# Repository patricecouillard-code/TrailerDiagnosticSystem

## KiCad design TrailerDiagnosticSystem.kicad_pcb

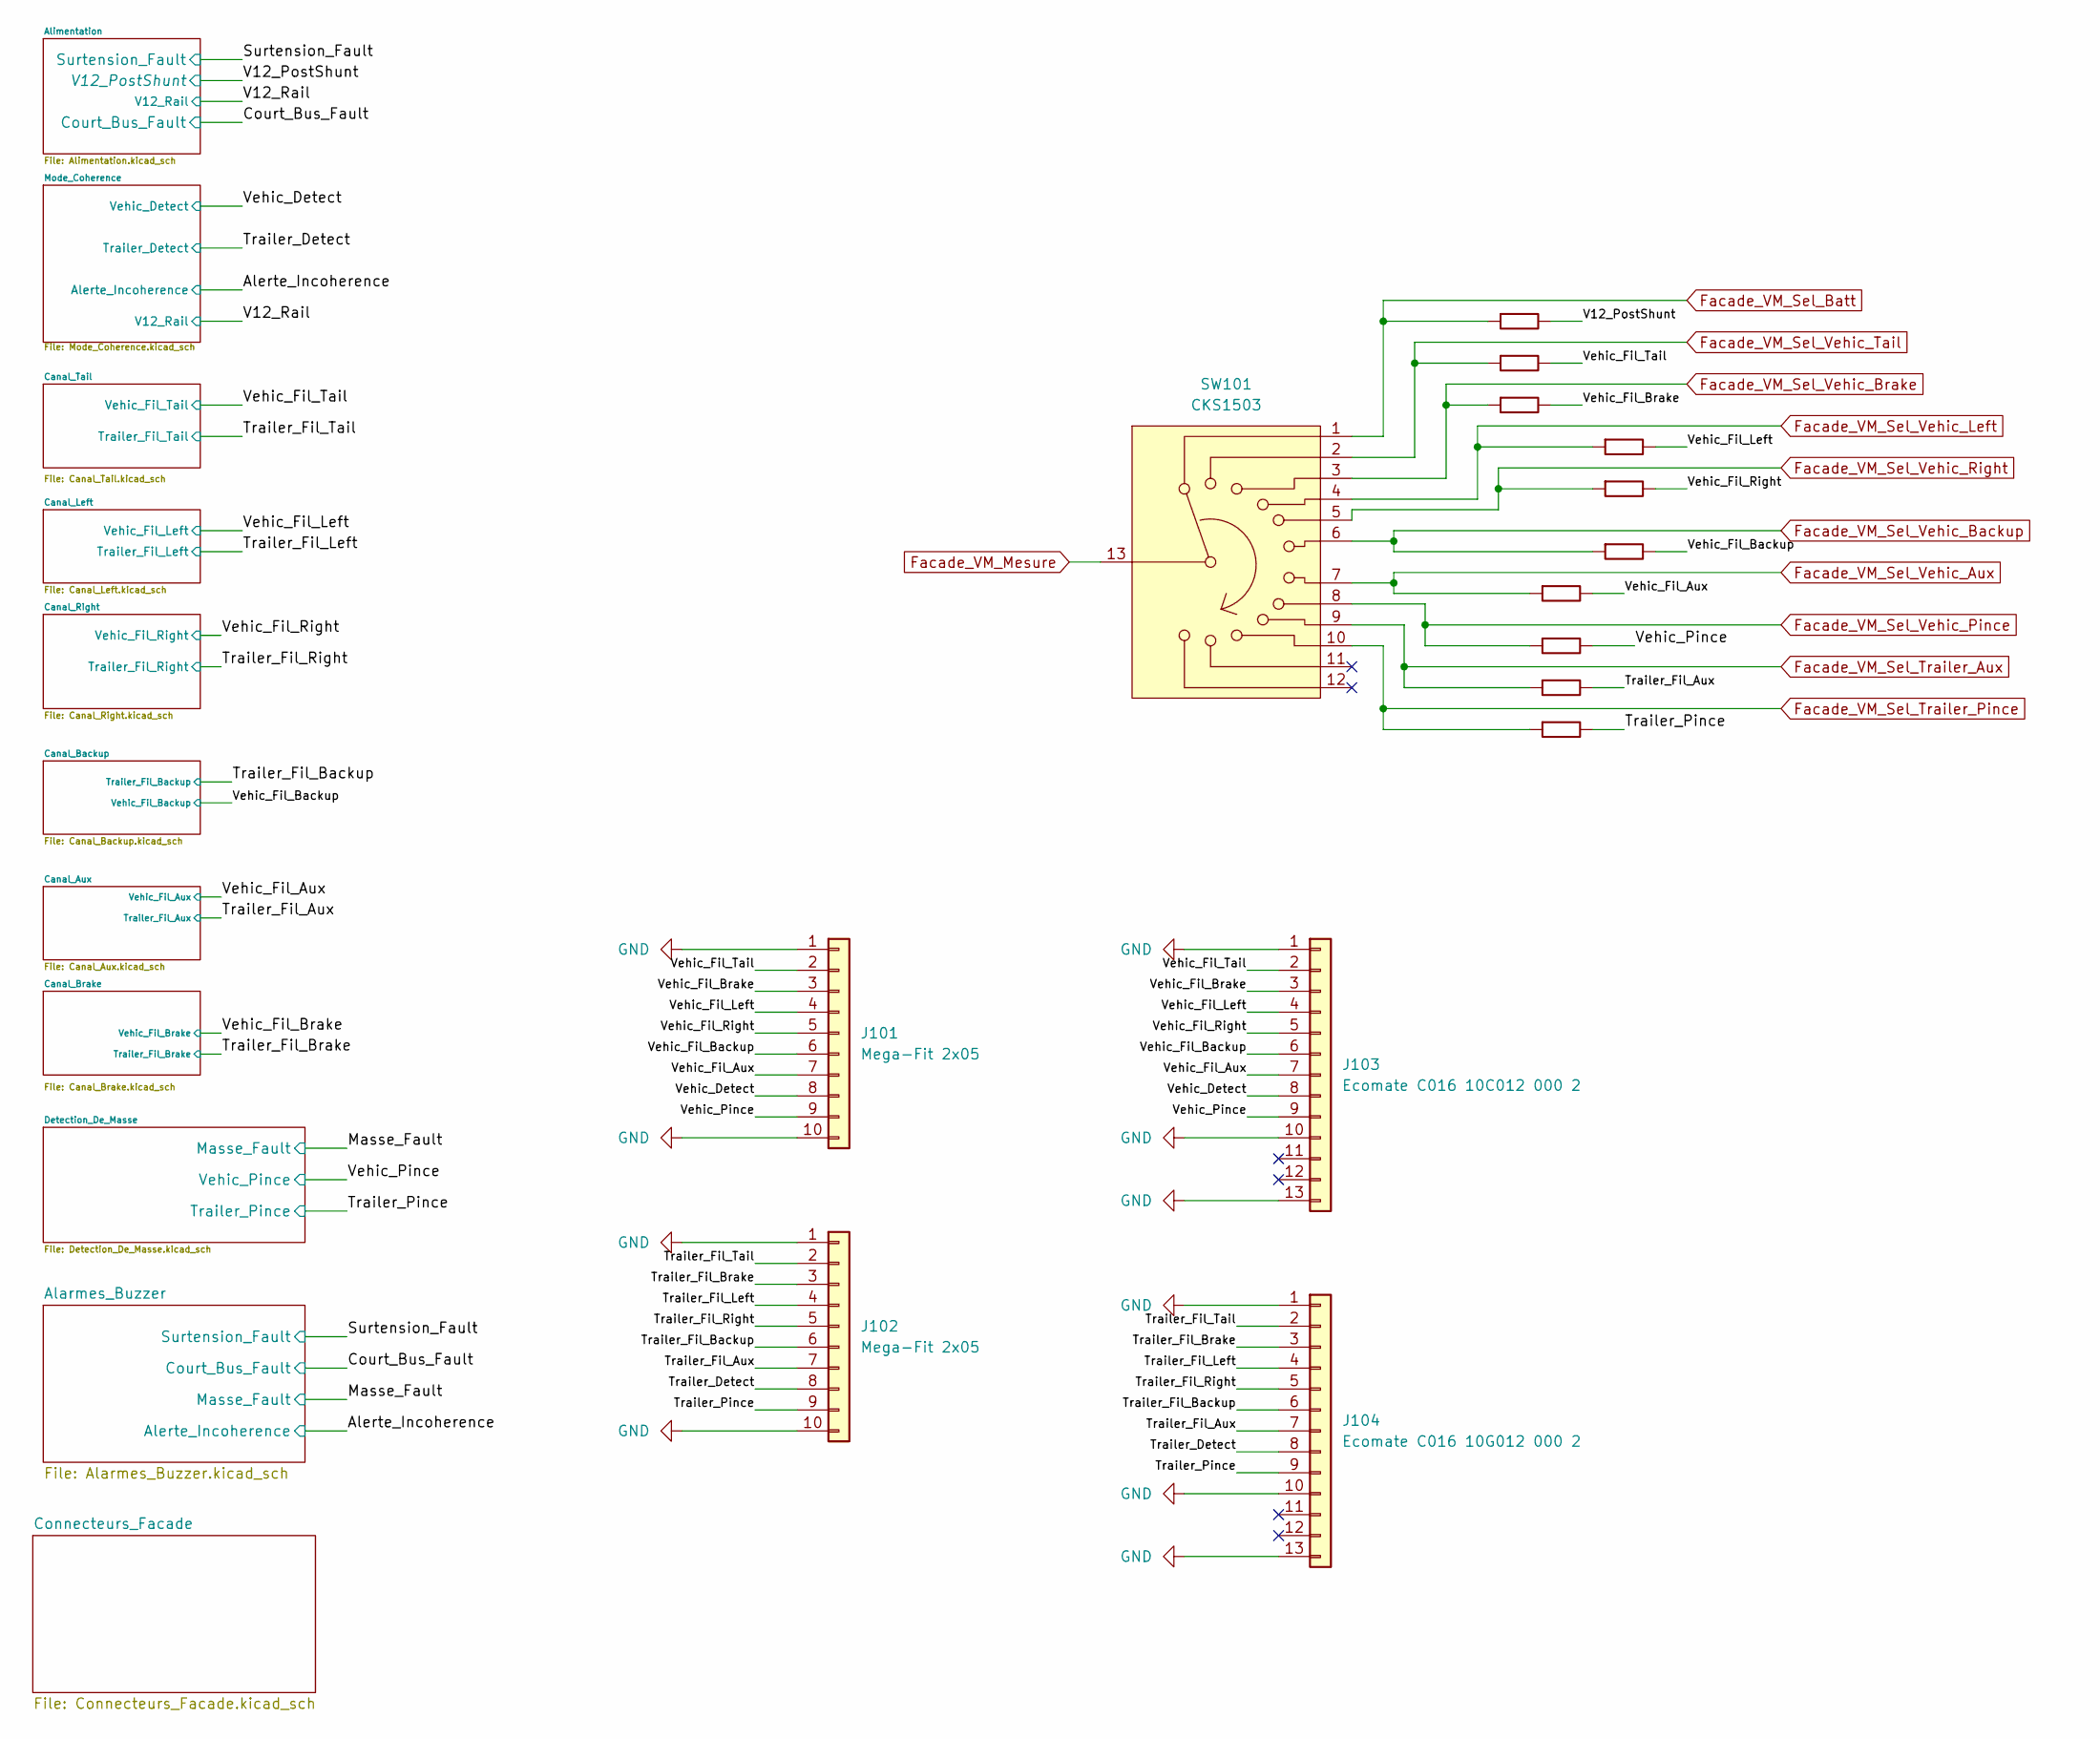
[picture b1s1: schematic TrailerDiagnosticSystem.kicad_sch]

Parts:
J101, J102: Mega-Fit 2x05; Molex_Mega-Fit_76829-0010_2x05_P5.70mm_Vertical
J103: Ecomate C016 10C012 000 2
J104: Ecomate C016 10G012 000 2
R101, R102, R103, R104, R105, R106, R107, R108, R109, R110: 1kΩ; R_Axial_DIN0309_L9.0mm_D3.2mm_P12.70mm_Horizontal
SW101: CKS1503

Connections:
/Trailer_Detect: J102.8, J104.8; also elsewhere on the board
/Trailer_Fil_Aux: J102.7, J104.7, R106.2; also elsewhere on the board
/Trailer_Fil_Backup: J102.6, J104.6; also elsewhere on the board
/Trailer_Fil_Brake: J102.3, J104.3; also elsewhere on the board
/Trailer_Fil_Left: J102.4, J104.4; also elsewhere on the board
/Trailer_Fil_Right: J102.5, J104.5; also elsewhere on the board
/Trailer_Fil_Tail: J102.2, J104.2; also elsewhere on the board
/Trailer_Pince: J102.9, J104.9, R107.2; also elsewhere on the board
/V12_PostShunt: R101.2; also elsewhere on the board
/Vehic_Detect: J101.8, J103.8; also elsewhere on the board
/Vehic_Fil_Aux: J101.7, J103.7, R104.2; also elsewhere on the board
/Vehic_Fil_Backup: J101.6, J103.6, R110.2; also elsewhere on the board
/Vehic_Fil_Brake: J101.3, J103.3, R103.2; also elsewhere on the board
/Vehic_Fil_Left: J101.4, J103.4, R108.2; also elsewhere on the board
/Vehic_Fil_Right: J101.5, J103.5, R109.2; also elsewhere on the board
/Vehic_Fil_Tail: J101.2, J103.2, R102.2; also elsewhere on the board
/Vehic_Pince: J101.9, J103.9, R105.2; also elsewhere on the board
Facade_VM_Sel_Batt: R101.1, SW101.1; also elsewhere on the board
Facade_VM_Sel_Trailer_Aux: R106.1, SW101.9; also elsewhere on the board
Facade_VM_Sel_Trailer_Pince: R107.1, SW101.10; also elsewhere on the board
Facade_VM_Sel_Vehic_Aux: R104.1, SW101.7; also elsewhere on the board
Facade_VM_Sel_Vehic_Backup: R110.1, SW101.6; also elsewhere on the board
Facade_VM_Sel_Vehic_Brake: R103.1, SW101.3; also elsewhere on the board
Facade_VM_Sel_Vehic_Left: R108.1, SW101.4; also elsewhere on the board
Facade_VM_Sel_Vehic_Pince: R105.1, SW101.8; also elsewhere on the board
Facade_VM_Sel_Vehic_Right: R109.1, SW101.5; also elsewhere on the board
Facade_VM_Sel_Vehic_Tail: R102.1, SW101.2; also elsewhere on the board
GND: J101.1, J101.10, J102.1, J102.10, J103.1, J103.10, J103.13, J104.1, J104.10, J104.13; also elsewhere on the board

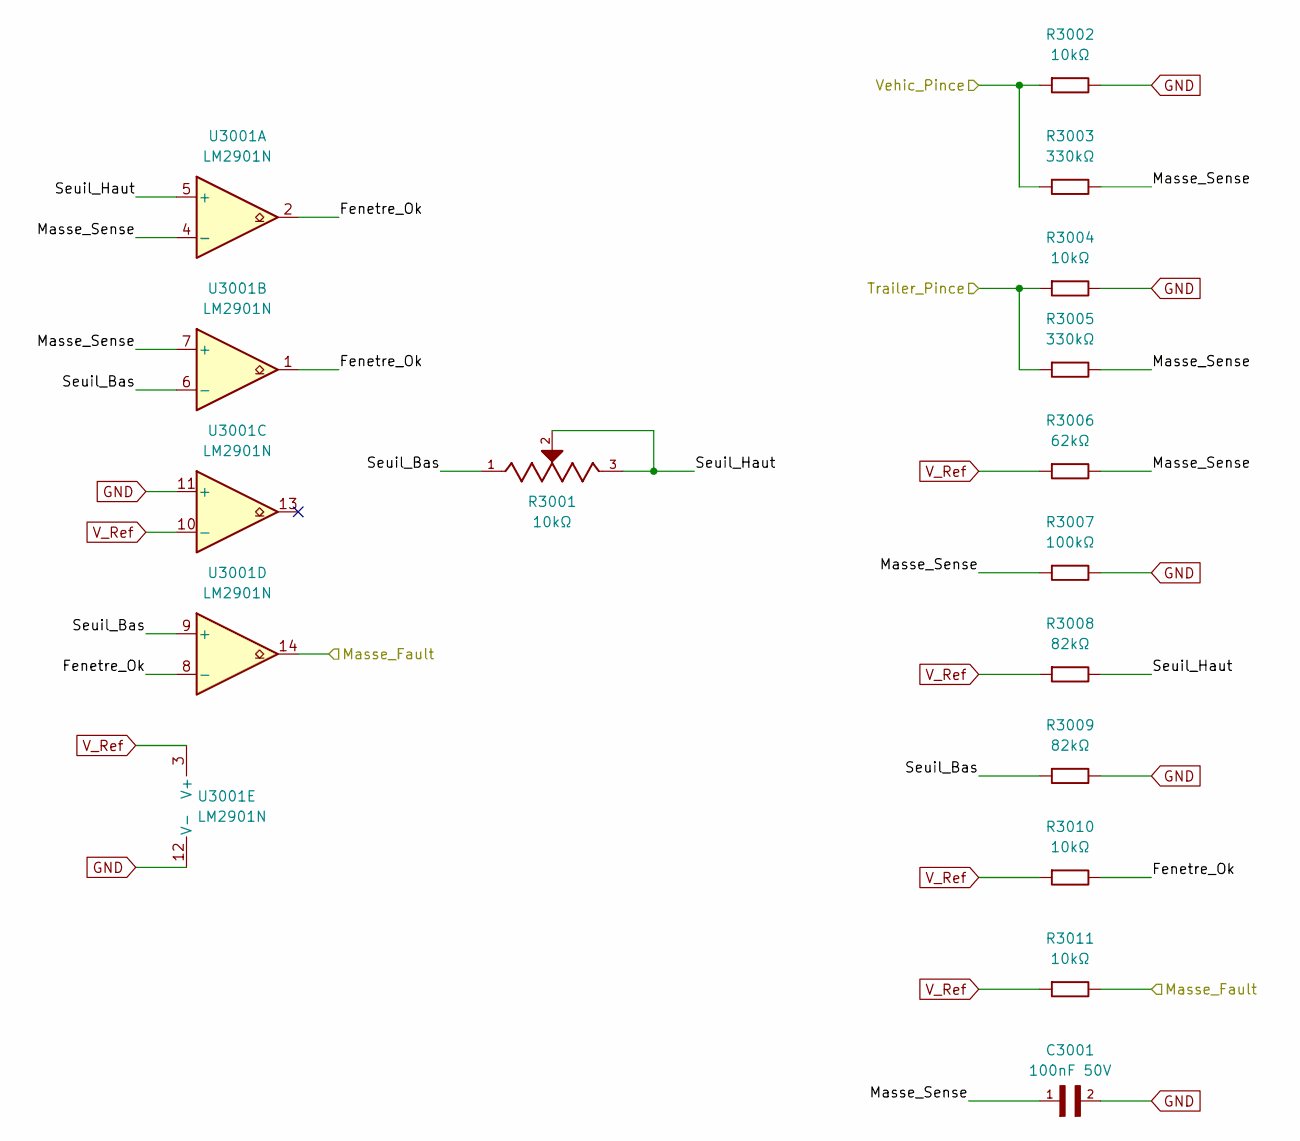
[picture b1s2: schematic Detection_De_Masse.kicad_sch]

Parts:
C3001: 100nF 50V; CAPRR254W50L508T317H508; MPN SR205C104KAR
R3001: 10kΩ; TRIM_3296W1103LF; MPN 3296W-1-103LF
R3002, R3004, R3010, R3011: 10kΩ; R_Axial_DIN0207_L6.3mm_D2.5mm_P10.16mm_Horizontal
R3003, R3005: 330kΩ; R_Axial_DIN0207_L6.3mm_D2.5mm_P10.16mm_Horizontal
R3006: 62kΩ; R_Axial_DIN0207_L6.3mm_D2.5mm_P10.16mm_Horizontal
R3007: 100kΩ; R_Axial_DIN0207_L6.3mm_D2.5mm_P10.16mm_Horizontal
R3008, R3009: 82kΩ; R_Axial_DIN0207_L6.3mm_D2.5mm_P10.16mm_Horizontal
U3001: LM2901N; DIP-14_W7.62mm_Socket

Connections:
/Detection_De_Masse/Fenetre_Ok: R3010.2, U3001.1, U3001.2, U3001.8 (-)
/Detection_De_Masse/Masse_Sense: C3001.1, R3003.2, R3005.2, R3006.2, R3007.1, U3001.4 (-), U3001.7 (+)
/Detection_De_Masse/Seuil_Bas: R3001.1, R3009.1, U3001.6 (-), U3001.9 (+)
/Detection_De_Masse/Seuil_Haut: R3001.2, R3001.3, R3008.2, U3001.5 (+)
/Masse_Fault: R3011.2, U3001.14; also elsewhere on the board
/Trailer_Pince: R3004.1, R3005.1; also elsewhere on the board
/Vehic_Pince: R3002.1, R3003.1; also elsewhere on the board
GND: C3001.2, R3002.2, R3004.2, R3007.2, R3009.2, U3001.11 (+), U3001.12 (V-); also elsewhere on the board
V_Ref: R3006.1, R3008.1, R3010.1, R3011.1, U3001.3 (V+), U3001.10 (-); also elsewhere on the board

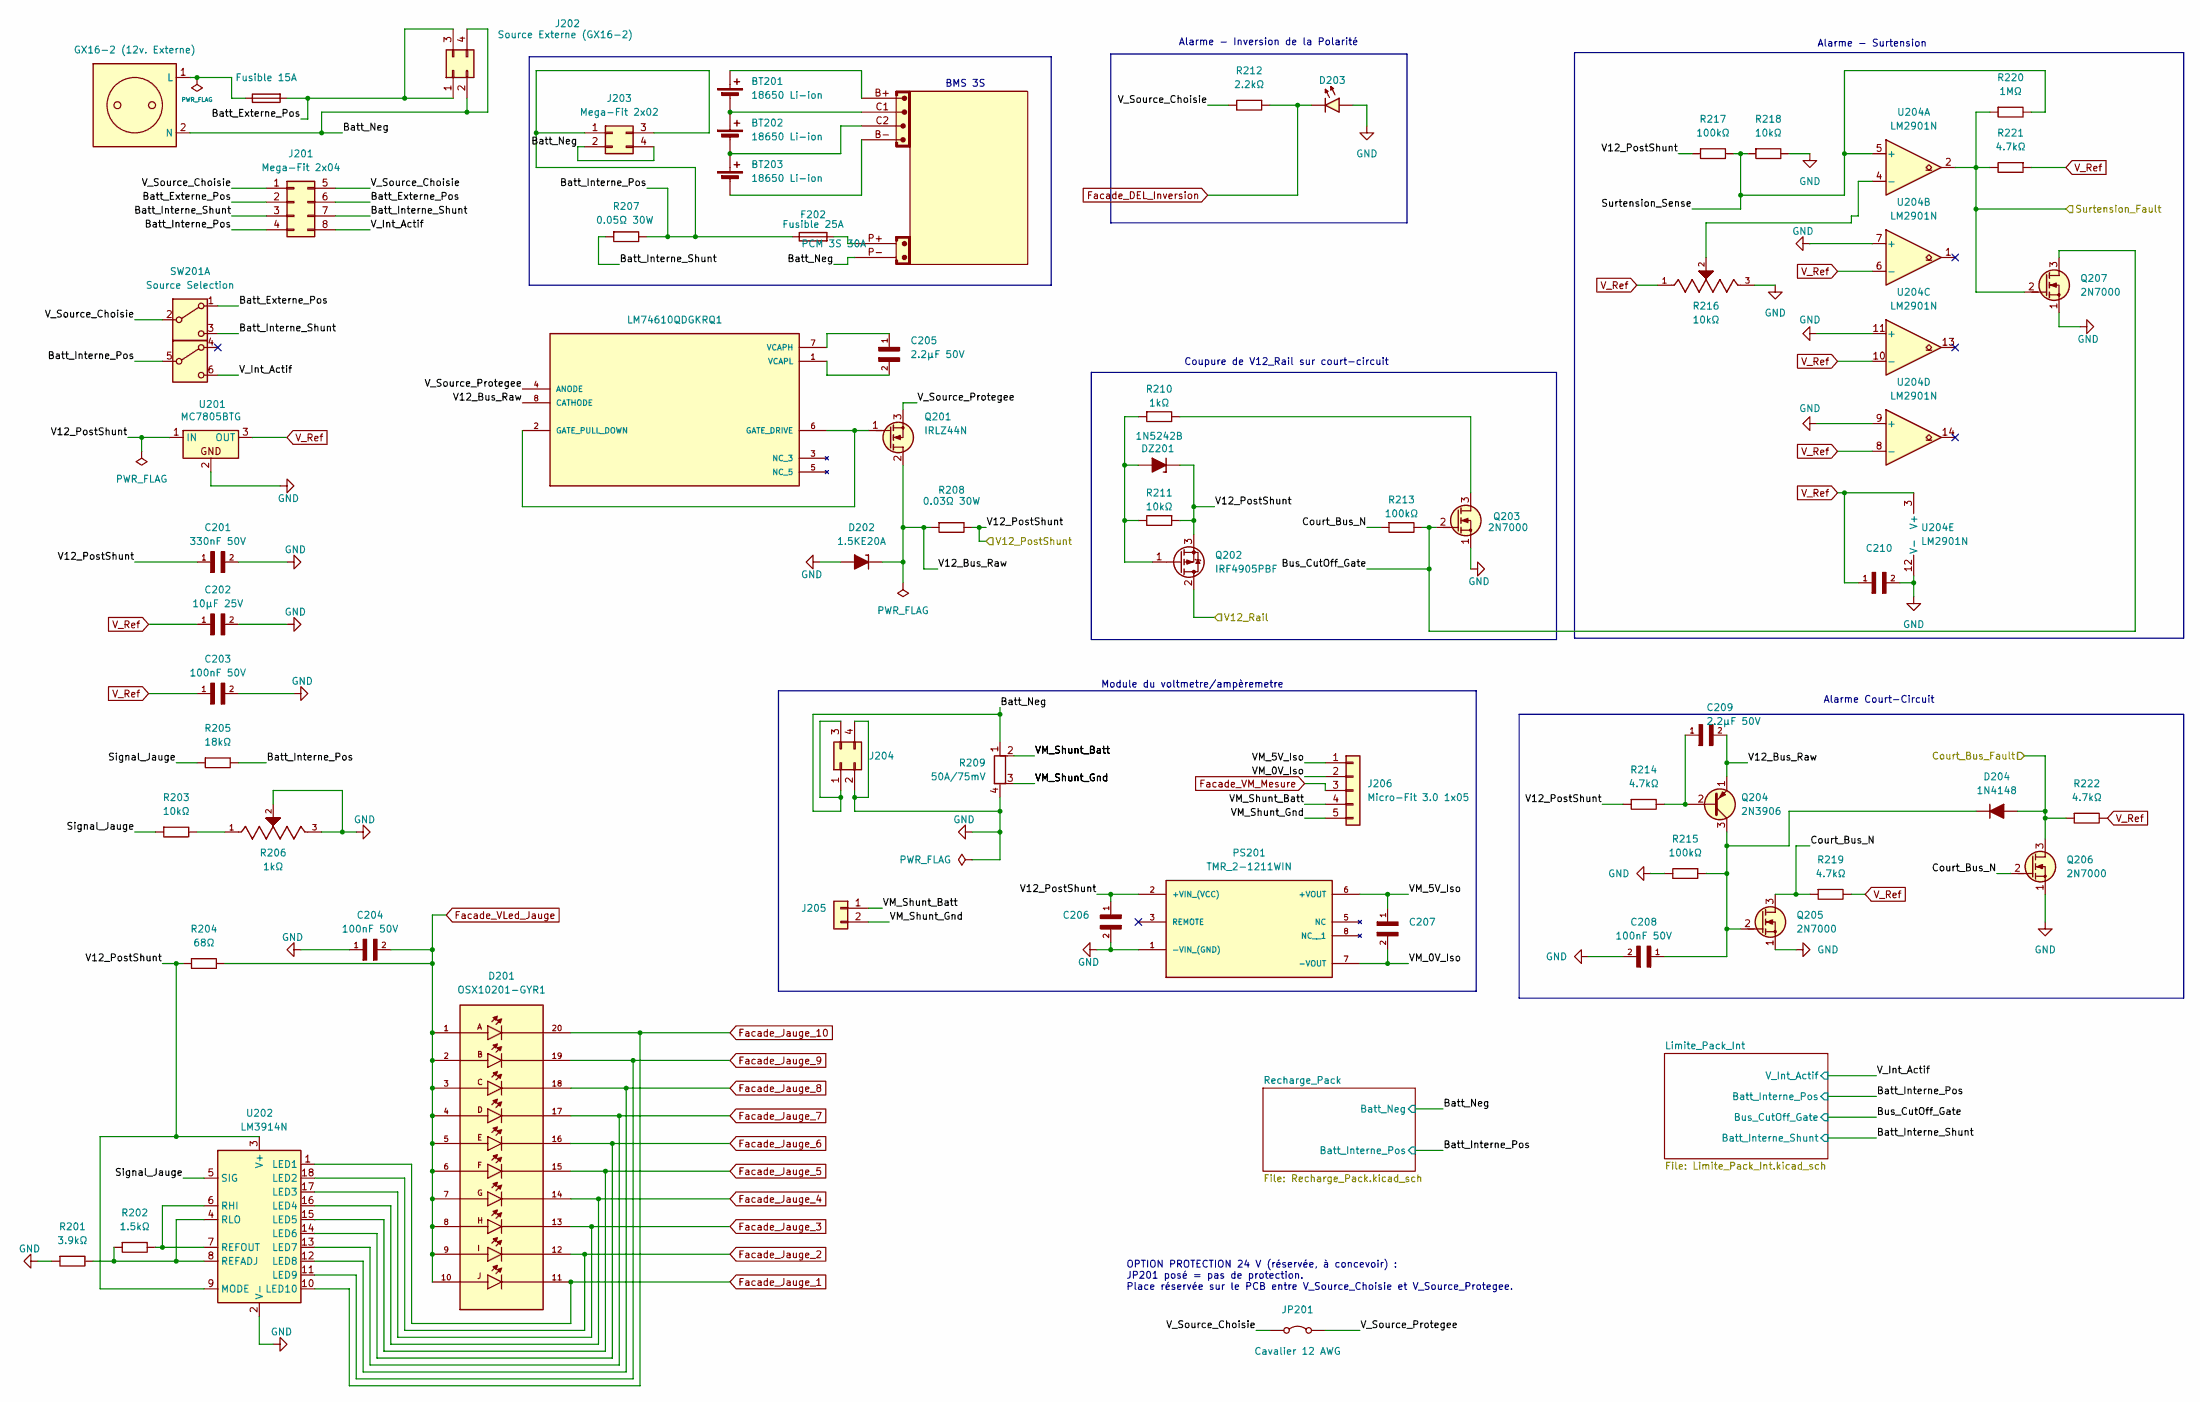
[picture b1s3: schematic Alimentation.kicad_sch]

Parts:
BMS201: PCM 3S 30A; MPN PCM-L04S30-566 (CU-J881, produit #7758)
BT201, BT202, BT203: 18650 Li-ion; MPN INR-18650-P28A
C201: 330nF 50V; CAPRR508W50L762T381H762; MPN SR305C334KAR
C202, C207: 10µF 25V; CAPRB500W50L550T350H600; MPN FG26X7R1E106KRT06
C203, C204, C208, C210: 100nF 50V; CAPRR254W50L508T317H508; MPN SR205C104KAR
C205, C209: 2.2µF 50V; CAPRB500W50L450T300H550; MPN FG24X7R1H225KRT06
C206: 10µF 50V; CAPRR508W50L762T381H762; MPN SR655C106KAR
D201: OSX10201-GYR1; DIP760W45P254L2550H815Q20B; PARTREV VER D.1.0
D202: 1.5KE20A; D_DO-201AE_P15.24mm_Horizontal
D203: RGB 5mm CA (rouge); LED_D5.0mm-4_RGB_Staggered_Pins; MPN WP154A4SEJ3VBDZGW/CA
D204: 1N4148; D_DO-35_SOD27_P7.62mm_Horizontal
DZ201: 1N5242B; D_DO-35_SOD27_P7.62mm_Horizontal_Zener
F201: Fusible 15A; MPN 0287015.PXCN
F202: Fusible 25A; MPN 0287025.PXCN
J201: Mega-Fit 2x04; Molex_Mega-Fit_76829-0008_2x04_P5.70mm_Vertical; MPN 0768290008
J202, J203, J204: Mega-Fit 2x02; Molex_Mega-Fit_76829-0004_2x02_P5.70mm_Vertical; MPN 0768290004
J205: Micro-Fit 3.0 1x02; Molex_Micro-Fit_3.0_43650-0215_1x02_P3.00mm_Vertical
J206: Micro-Fit 3.0 1x05; Molex_Micro-Fit_3.0_43650-0515_1x05_P3.00mm_Vertical
JP201: Cavalier 12 AWG; SolderWire-2.5sqmm_1x02_P8.8mm_D2.4mm_OD4.4mm
P201: Batt. ext. 2P
PS201: TMR_2-1211WIN; CONV_TMR_2-1211WIN; PARTREV January 27, 2021
Q201: IRLZ44N; TO-220-3_Vertical_GDS
Q202: IRF4905PBF; TO-220-3_Vertical; MPN IRF4905PBF
Q203, Q205, Q206, Q207: 2N7000; TO-92_Inline_Wide_SGD
Q204: 2N3906; TO-92_Inline_Wide_EBC
R201: 3.9kΩ; R_Axial_DIN0207_L6.3mm_D2.5mm_P10.16mm_Horizontal
R202: 1.5kΩ; R_Axial_DIN0207_L6.3mm_D2.5mm_P10.16mm_Horizontal
R203, R211, R218: 10kΩ; R_Axial_DIN0207_L6.3mm_D2.5mm_P10.16mm_Horizontal
R204: 68Ω; R_Axial_Power_L25.0mm_W9.0mm_P27.94mm
R205: 18kΩ; R_Axial_DIN0207_L6.3mm_D2.5mm_P10.16mm_Horizontal
R206: 1kΩ; TRIM_3296W-1-102LF; MPN 3296W-1-102LF
R207: 0.05Ω 30W; TO-220-2_Vertical; MPN MP930-0.050-1%
R208: 0.03Ω 30W; TO-220-2_Vertical; MPN MP930-0.030-5%
R209: 50A/75mV
R210: 1kΩ; R_Axial_DIN0207_L6.3mm_D2.5mm_P10.16mm_Horizontal
R212: 2.2kΩ; R_Axial_DIN0207_L6.3mm_D2.5mm_P10.16mm_Horizontal
R213, R215, R217: 100kΩ; R_Axial_DIN0207_L6.3mm_D2.5mm_P10.16mm_Horizontal
R214, R219, R221, R222: 4.7kΩ; R_Axial_DIN0207_L6.3mm_D2.5mm_P10.16mm_Horizontal
R216: 10kΩ; TRIM_3296W1103LF; MPN 3296W-1-103LF
R220: 1MΩ; R_Axial_DIN0207_L6.3mm_D2.5mm_P10.16mm_Horizontal
SW201: Cole Hersee 5592
U201: MC7805BTG; TO-220-3_Vertical
U202: LM3914N; DIP-18_W7.62mm_Socket
U203: LM74610QDGKRQ1; SOP65P490X110-8N; PARTREV B
U204: LM2901N; DIP-14_W7.62mm_Socket

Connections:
/Alimentation/Batt_Externe_Pos: F201.2, J201.2, J201.6, J202.1, J202.3, SW201.1 (A)
/Alimentation/Batt_Interne_Pos: F202.1, J201.4, J203.1, J203.3, R205.2, R207.2, SW201.5 (B); also elsewhere on the board
/Alimentation/Batt_Interne_Shunt: J201.3, J201.7, R207.1, SW201.3 (C); also elsewhere on the board
/Alimentation/Batt_Neg: BMS201.P-, J202.2, J202.4, J203.2, J203.4, J204.1, J204.3, P201.2 (N), R209.1; also elsewhere on the board
/Alimentation/Bus_CutOff_Gate: Q203.2 (G), Q207.3 (D), R213.2; also elsewhere on the board
/Alimentation/Court_Bus_N: Q205.3 (D), Q206.2 (G), R213.1, R219.1
/Alimentation/Signal_Jauge: R203.1, R205.1, U202.5 (SIG)
/Alimentation/Surtension_Sense: R217.2, R218.1, R220.2, U204.5 (+)
/Alimentation/V12_Bus_Raw: C209.2, D202.1 (K), Q201.2 (D), Q204.1 (E), R208.1, U203.8 (CATHODE)
/Alimentation/VM_0V_Iso: C207.2, J206.2, PS201.7 (-VOUT)
/Alimentation/VM_5V_Iso: C207.1, J206.1, PS201.6 (+VOUT)
/Alimentation/VM_Shunt_Batt: J205.1, J206.4, R209.2
/Alimentation/VM_Shunt_Gnd: J205.2, J206.5, R209.3
/Alimentation/V_Int_Actif: J201.8, SW201.6 (C); also elsewhere on the board
/Alimentation/V_Source_Choisie: J201.1, J201.5, JP201.1 (A), R212.2, SW201.2 (B)
/Alimentation/V_Source_Protegee: JP201.2 (B), Q201.3 (S), U203.4 (ANODE)
/Court_Bus_Fault: D204.2 (A), Q206.3 (D), R222.1; also elsewhere on the board
/Surtension_Fault: Q207.2 (G), R220.1, R221.2, U204.2; also elsewhere on the board
/V12_PostShunt: C201.1, C206.1, DZ201.1 (K), PS201.2 (+VIN_(VCC)), Q202.3 (S), R204.1, R208.2, R211.1, R214.1, R217.1, U201.1 (IN), U202.3 (V+), U202.9 (MODE); also elsewhere on the board
/V12_Rail: Q202.2 (D); also elsewhere on the board
Facade_DEL_Inversion: D203.1 (K), R212.1; also elsewhere on the board
Facade_Jauge_1: D201.11, U202.1 (LED1); also elsewhere on the board
Facade_Jauge_2: D201.12, U202.18 (LED2); also elsewhere on the board
Facade_Jauge_3: D201.13, U202.17 (LED3); also elsewhere on the board
Facade_Jauge_4: D201.14, U202.16 (LED4); also elsewhere on the board
Facade_Jauge_5: D201.15, U202.15 (LED5); also elsewhere on the board
Facade_Jauge_6: D201.16, U202.14 (LED6); also elsewhere on the board
Facade_Jauge_7: D201.17, U202.13 (LED7); also elsewhere on the board
Facade_Jauge_8: D201.18, U202.12 (LED8); also elsewhere on the board
Facade_Jauge_9: D201.19, U202.11 (LED9); also elsewhere on the board
Facade_Jauge_10: D201.20, U202.10 (LED10); also elsewhere on the board
Facade_VLed_Jauge: C204.2, D201.1, D201.2, D201.3, D201.4, D201.5, D201.6, D201.7, D201.8, D201.9, D201.10, R204.2; also elsewhere on the board
Facade_VM_Mesure: J206.3; also elsewhere on the board
GND: C201.2, C202.2, C203.2, C204.1, C206.2, C208.2, C210.2, D202.2 (A), D203.2 (A), J204.2, J204.4, PS201.1 (-VIN_(GND)), Q203.1 (S), Q205.1 (S), Q206.1 (S), Q207.1 (S), R201.1, R206.2, R206.3, R209.4, R215.2, R216.3, R218.2, U201.2, U202.2 (V-), U204.7 (+), U204.9 (+), U204.11 (+), U204.12 (V-); also elsewhere on the board
unnamed: BMS201.B+, BT201.1 (+)
unnamed: BMS201.B-, BT203.2 (-)
unnamed: BMS201.C1, BT201.2 (-), BT202.1 (+)
unnamed: BMS201.C2, BT202.2 (-), BT203.1 (+)
unnamed: BMS201.P+, F202.2
unnamed: C208.1, D204.1 (K), Q204.3 (C), Q205.2 (G), R215.1
unnamed: DZ201.2 (A), Q202.1 (G), R210.1, R211.2
unnamed: F201.1, P201.1 (L)
unnamed: Q201.1 (G), U203.2 (GATE_PULL_DOWN), U203.6 (GATE_DRIVE)
unnamed: Q203.3 (D), R210.2
unnamed: C209.1, Q204.2 (B), R214.2
unnamed: R203.2, R206.1
unnamed: R201.2, R202.1, U202.4 (RLO), U202.8 (REFADJ)
unnamed: R202.2, U202.6 (RHI), U202.7 (REFOUT)
unnamed: C205.1, U203.7 (VCAPH)
unnamed: C205.2, U203.1 (VCAPL)
unnamed: R216.2, U204.4 (-)
V_Ref: C202.1, C203.1, C210.1, R216.1, R219.2, R221.1, R222.2, U201.3 (OUT), U204.3 (V+), U204.6 (-), U204.8 (-), U204.10 (-); also elsewhere on the board

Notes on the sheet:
Module du voltmetre/ampèremetre
Alarme - Inversion de la Polarité
OPTION PROTECTION 24 V (réservée, à concevoir) : JP201 posé = pas de protection. Place réservée sur le PCB entre V_Source_Choisie et V_Source_Protegee.
Alarme - Surtension
Alarme Court-Circuit
BMS 3S
Coupure de V12_Rail sur court-circuit

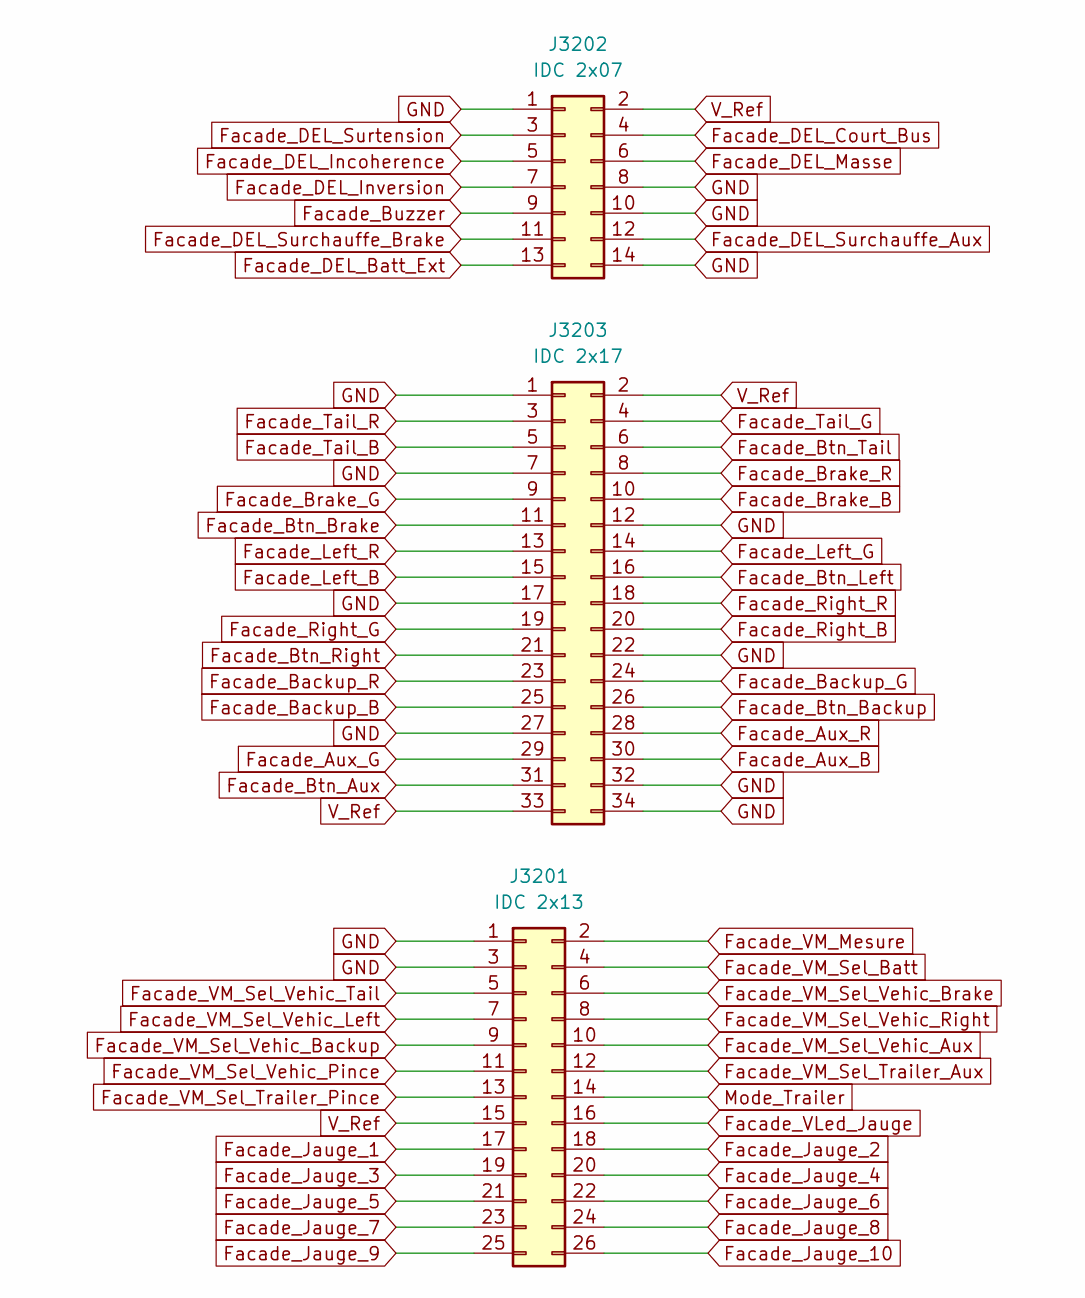
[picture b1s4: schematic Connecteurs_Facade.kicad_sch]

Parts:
J3201: IDC 2x13; IDC-Header_2x13_P2.54mm_Latch_Vertical; MPN N3429-6302RB
J3202: IDC 2x07; IDC-Header_2x07_P2.54mm_Latch_Vertical; MPN N3314-6302RB
J3203: IDC 2x17; IDC-Header_2x17_P2.54mm_Latch_Vertical; MPN N3431-6302RB

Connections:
Facade_Aux_B: J3203.30; also elsewhere on the board
Facade_Aux_G: J3203.29; also elsewhere on the board
Facade_Aux_R: J3203.28; also elsewhere on the board
Facade_Backup_B: J3203.25; also elsewhere on the board
Facade_Backup_G: J3203.24; also elsewhere on the board
Facade_Backup_R: J3203.23; also elsewhere on the board
Facade_Brake_B: J3203.10; also elsewhere on the board
Facade_Brake_G: J3203.9; also elsewhere on the board
Facade_Brake_R: J3203.8; also elsewhere on the board
Facade_Btn_Aux: J3203.31; also elsewhere on the board
Facade_Btn_Backup: J3203.26; also elsewhere on the board
Facade_Btn_Brake: J3203.11; also elsewhere on the board
Facade_Btn_Left: J3203.16; also elsewhere on the board
Facade_Btn_Right: J3203.21; also elsewhere on the board
Facade_Btn_Tail: J3203.6; also elsewhere on the board
Facade_Buzzer: J3202.9; also elsewhere on the board
Facade_DEL_Batt_Ext: J3202.13; also elsewhere on the board
Facade_DEL_Court_Bus: J3202.4; also elsewhere on the board
Facade_DEL_Incoherence: J3202.5; also elsewhere on the board
Facade_DEL_Inversion: J3202.7; also elsewhere on the board
Facade_DEL_Masse: J3202.6; also elsewhere on the board
Facade_DEL_Surchauffe_Aux: J3202.12; also elsewhere on the board
Facade_DEL_Surchauffe_Brake: J3202.11; also elsewhere on the board
Facade_DEL_Surtension: J3202.3; also elsewhere on the board
Facade_Jauge_1: J3201.17; also elsewhere on the board
Facade_Jauge_2: J3201.18; also elsewhere on the board
Facade_Jauge_3: J3201.19; also elsewhere on the board
Facade_Jauge_4: J3201.20; also elsewhere on the board
Facade_Jauge_5: J3201.21; also elsewhere on the board
Facade_Jauge_6: J3201.22; also elsewhere on the board
Facade_Jauge_7: J3201.23; also elsewhere on the board
Facade_Jauge_8: J3201.24; also elsewhere on the board
Facade_Jauge_9: J3201.25; also elsewhere on the board
Facade_Jauge_10: J3201.26; also elsewhere on the board
Facade_Left_B: J3203.15; also elsewhere on the board
Facade_Left_G: J3203.14; also elsewhere on the board
Facade_Left_R: J3203.13; also elsewhere on the board
Facade_Right_B: J3203.20; also elsewhere on the board
Facade_Right_G: J3203.19; also elsewhere on the board
Facade_Right_R: J3203.18; also elsewhere on the board
Facade_Tail_B: J3203.5; also elsewhere on the board
Facade_Tail_G: J3203.4; also elsewhere on the board
Facade_Tail_R: J3203.3; also elsewhere on the board
Facade_VLed_Jauge: J3201.16; also elsewhere on the board
Facade_VM_Mesure: J3201.2; also elsewhere on the board
Facade_VM_Sel_Batt: J3201.4; also elsewhere on the board
Facade_VM_Sel_Trailer_Aux: J3201.12; also elsewhere on the board
Facade_VM_Sel_Trailer_Pince: J3201.13; also elsewhere on the board
Facade_VM_Sel_Vehic_Aux: J3201.10; also elsewhere on the board
Facade_VM_Sel_Vehic_Backup: J3201.9; also elsewhere on the board
Facade_VM_Sel_Vehic_Brake: J3201.6; also elsewhere on the board
Facade_VM_Sel_Vehic_Left: J3201.7; also elsewhere on the board
Facade_VM_Sel_Vehic_Pince: J3201.11; also elsewhere on the board
Facade_VM_Sel_Vehic_Right: J3201.8; also elsewhere on the board
Facade_VM_Sel_Vehic_Tail: J3201.5; also elsewhere on the board
GND: J3201.1, J3201.3, J3202.1, J3202.8, J3202.10, J3202.14, J3203.1, J3203.7, J3203.12, J3203.17, J3203.22, J3203.27, J3203.32, J3203.34; also elsewhere on the board
Mode_Trailer: J3201.14; also elsewhere on the board
V_Ref: J3201.15, J3202.2, J3203.2, J3203.33; also elsewhere on the board

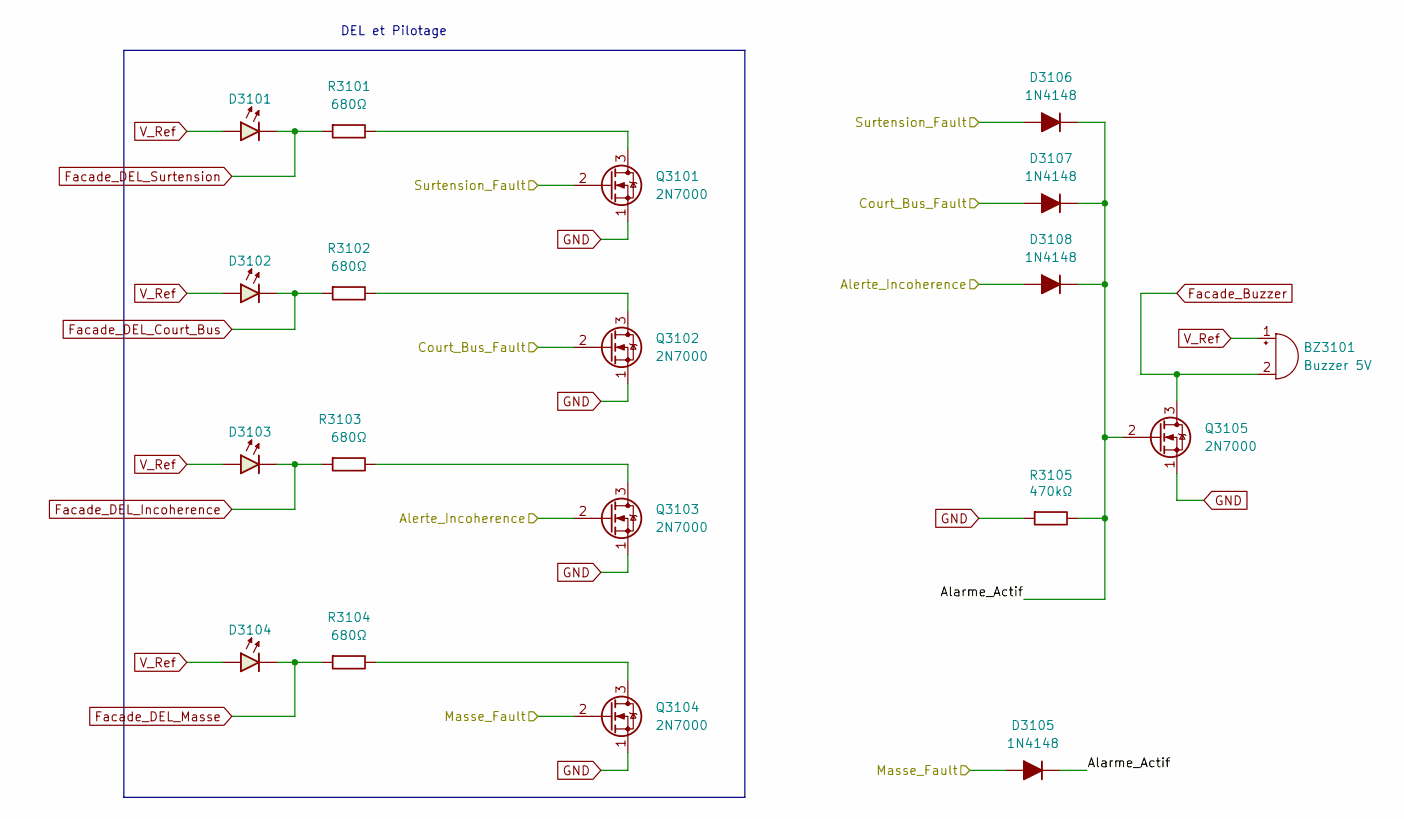
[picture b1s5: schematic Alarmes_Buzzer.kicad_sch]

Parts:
BZ3101: Buzzer 5V; MPN CMI-1295IC-0585T
D3101, D3102, D3103, D3104: RGB 5mm CA (rouge); LED_D5.0mm-4_RGB_Staggered_Pins; MPN WP154A4SEJ3VBDZGW/CA
D3105, D3106, D3107, D3108: 1N4148; D_DO-35_SOD27_P7.62mm_Horizontal
Q3101, Q3102, Q3103, Q3104, Q3105: 2N7000; TO-92_Inline_Wide_SGD
R3101, R3102, R3103, R3104: 680Ω; R_Axial_DIN0207_L6.3mm_D2.5mm_P10.16mm_Horizontal
R3105: 470kΩ; R_Axial_DIN0207_L6.3mm_D2.5mm_P10.16mm_Horizontal

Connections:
/Alarmes_Buzzer/Alarme_Actif: D3105.1 (K), D3106.1 (K), D3107.1 (K), D3108.1 (K), Q3105.2 (G), R3105.2
/Alerte_Incoherence: D3108.2 (A), Q3103.2 (G); also elsewhere on the board
/Court_Bus_Fault: D3107.2 (A), Q3102.2 (G); also elsewhere on the board
/Masse_Fault: D3105.2 (A), Q3104.2 (G); also elsewhere on the board
/Surtension_Fault: D3106.2 (A), Q3101.2 (G); also elsewhere on the board
Facade_Buzzer: BZ3101.2 (-), Q3105.3 (D); also elsewhere on the board
Facade_DEL_Court_Bus: D3102.1 (K), R3102.1; also elsewhere on the board
Facade_DEL_Incoherence: D3103.1 (K), R3103.1; also elsewhere on the board
Facade_DEL_Masse: D3104.1 (K), R3104.1; also elsewhere on the board
Facade_DEL_Surtension: D3101.1 (K), R3101.1; also elsewhere on the board
GND: Q3101.1 (S), Q3102.1 (S), Q3103.1 (S), Q3104.1 (S), Q3105.1 (S), R3105.1; also elsewhere on the board
unnamed: BZ3101.1 (+), D3101.2 (A), D3102.2 (A), D3103.2 (A), D3104.2 (A)
unnamed: Q3101.3 (D), R3101.2
unnamed: Q3102.3 (D), R3102.2
unnamed: Q3103.3 (D), R3103.2
unnamed: Q3104.3 (D), R3104.2

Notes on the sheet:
DEL et Pilotage

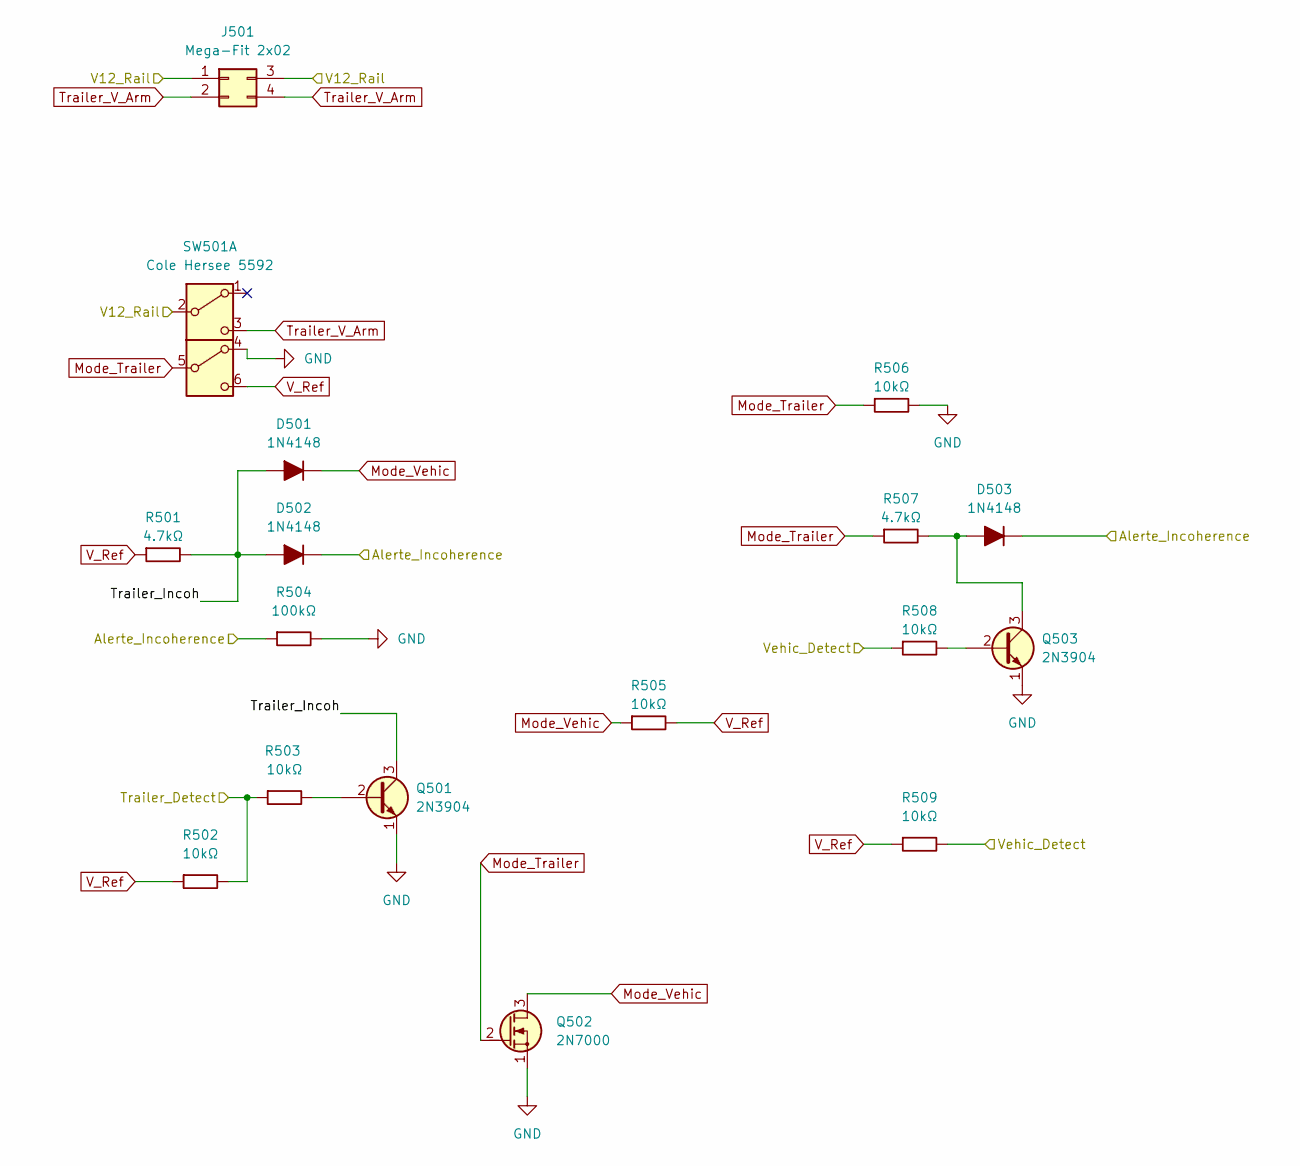
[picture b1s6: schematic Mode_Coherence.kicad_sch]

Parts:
D501, D502, D503: 1N4148; D_DO-35_SOD27_P7.62mm_Horizontal
J501: Mega-Fit 2x02; Molex_Mega-Fit_76829-0004_2x02_P5.70mm_Vertical; MPN 0768290004
Q501, Q503: 2N3904; TO-92_Inline_Wide_EBC
Q502: 2N7000; TO-92_Inline_Wide_SGD
R501, R507: 4.7kΩ; R_Axial_DIN0207_L6.3mm_D2.5mm_P10.16mm_Horizontal
R502, R503, R505, R506, R508, R509: 10kΩ; R_Axial_DIN0207_L6.3mm_D2.5mm_P10.16mm_Horizontal
R504: 100kΩ; R_Axial_DIN0207_L6.3mm_D2.5mm_P10.16mm_Horizontal
SW501: Cole Hersee 5592

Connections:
/Alerte_Incoherence: D502.1 (K), D503.1 (K), R504.1; also elsewhere on the board
/Mode_Coherence/Trailer_Incoh: D501.2 (A), D502.2 (A), Q501.3 (C), R501.2
/Trailer_Detect: R502.2, R503.1; also elsewhere on the board
/V12_Rail: J501.1, J501.3, SW501.2 (B); also elsewhere on the board
/Vehic_Detect: R508.1, R509.2; also elsewhere on the board
GND: Q501.1 (E), Q502.1 (S), Q503.1 (E), R504.2, R506.2, SW501.4 (A); also elsewhere on the board
Mode_Trailer: Q502.2 (G), R506.1, R507.1, SW501.5 (B); also elsewhere on the board
Mode_Vehic: D501.1 (K), Q502.3 (D), R505.1; also elsewhere on the board
unnamed: D503.2 (A), Q503.3 (C), R507.2
unnamed: Q501.2 (B), R503.2
unnamed: Q503.2 (B), R508.2
Trailer_V_Arm: J501.2, J501.4, SW501.3 (C); also elsewhere on the board
V_Ref: R501.1, R502.1, R505.2, R509.1, SW501.6 (C); also elsewhere on the board
